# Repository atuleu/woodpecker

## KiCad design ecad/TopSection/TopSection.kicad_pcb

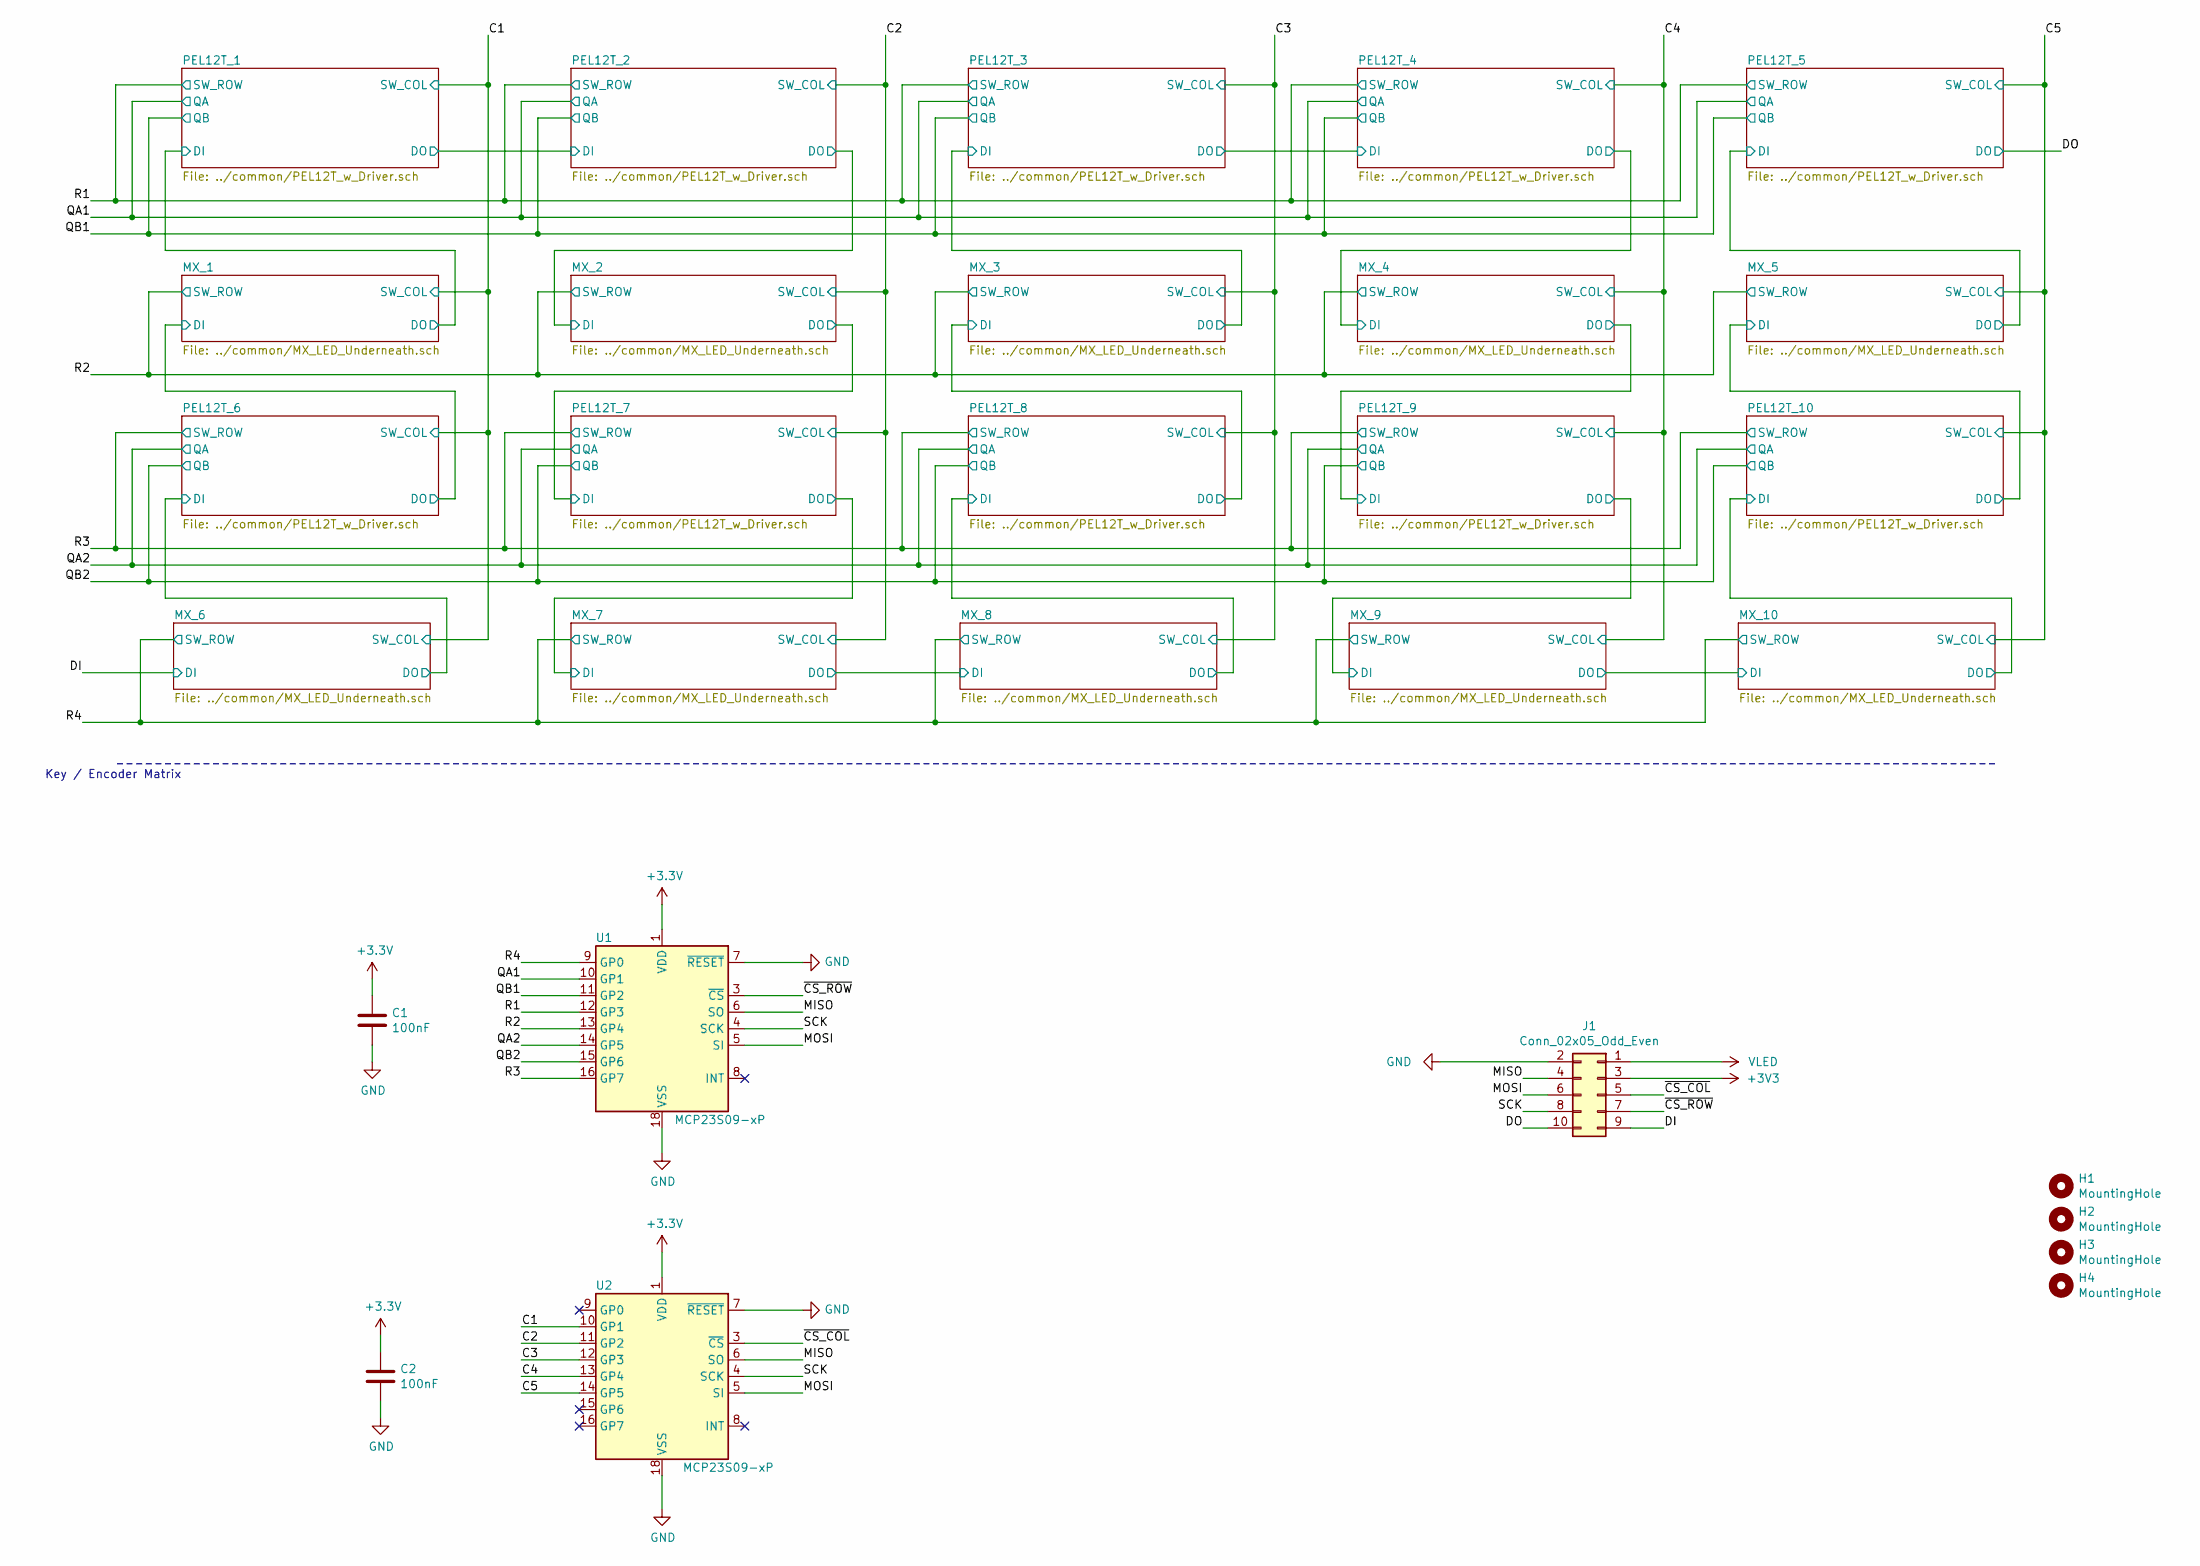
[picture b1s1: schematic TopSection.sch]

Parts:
C1, C2: 100nF; C_0603_1608Metric_Pad1.08x0.95mm_HandSolder
H1, H2, H3, H4: MountingHole; MountingHole_3.2mm_M3_DIN965
J1: Conn_02x05_Odd_Even; ConnectorMicromatch-10
U1, U2: MCP23S09-xP; DIP-18_W7.62mm

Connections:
/C1: U2.10 (GP1); also elsewhere on the board
/C2: U2.11 (GP2); also elsewhere on the board
/C3: U2.12 (GP3); also elsewhere on the board
/C4: U2.13 (GP4); also elsewhere on the board
/C5: U2.14 (GP5); also elsewhere on the board
/DI: J1.9; also elsewhere on the board
/DO: J1.10; also elsewhere on the board
/MISO: J1.4, U1.6 (SO), U2.6 (SO)
/MOSI: J1.6, U1.5 (SI), U2.5 (SI)
/QA1: U1.10 (GP1); also elsewhere on the board
/QA2: U1.14 (GP5); also elsewhere on the board
/QB1: U1.11 (GP2); also elsewhere on the board
/QB2: U1.15 (GP6); also elsewhere on the board
/R1: U1.12 (GP3); also elsewhere on the board
/R2: U1.13 (GP4); also elsewhere on the board
/R3: U1.16 (GP7); also elsewhere on the board
/R4: U1.9 (GP0); also elsewhere on the board
/SCK: J1.8, U1.4 (SCK), U2.4 (SCK)
/~CS_COL: J1.5, U2.3 (~CS)
/~CS_ROW: J1.7, U1.3 (~CS)
GND: C1.2, C2.2, J1.2, U1.7 (~RESET), U1.18 (VSS), U2.7 (~RESET), U2.18 (VSS); also elsewhere on the board
VLED: J1.1; also elsewhere on the board

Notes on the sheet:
Key / Encoder Matrix

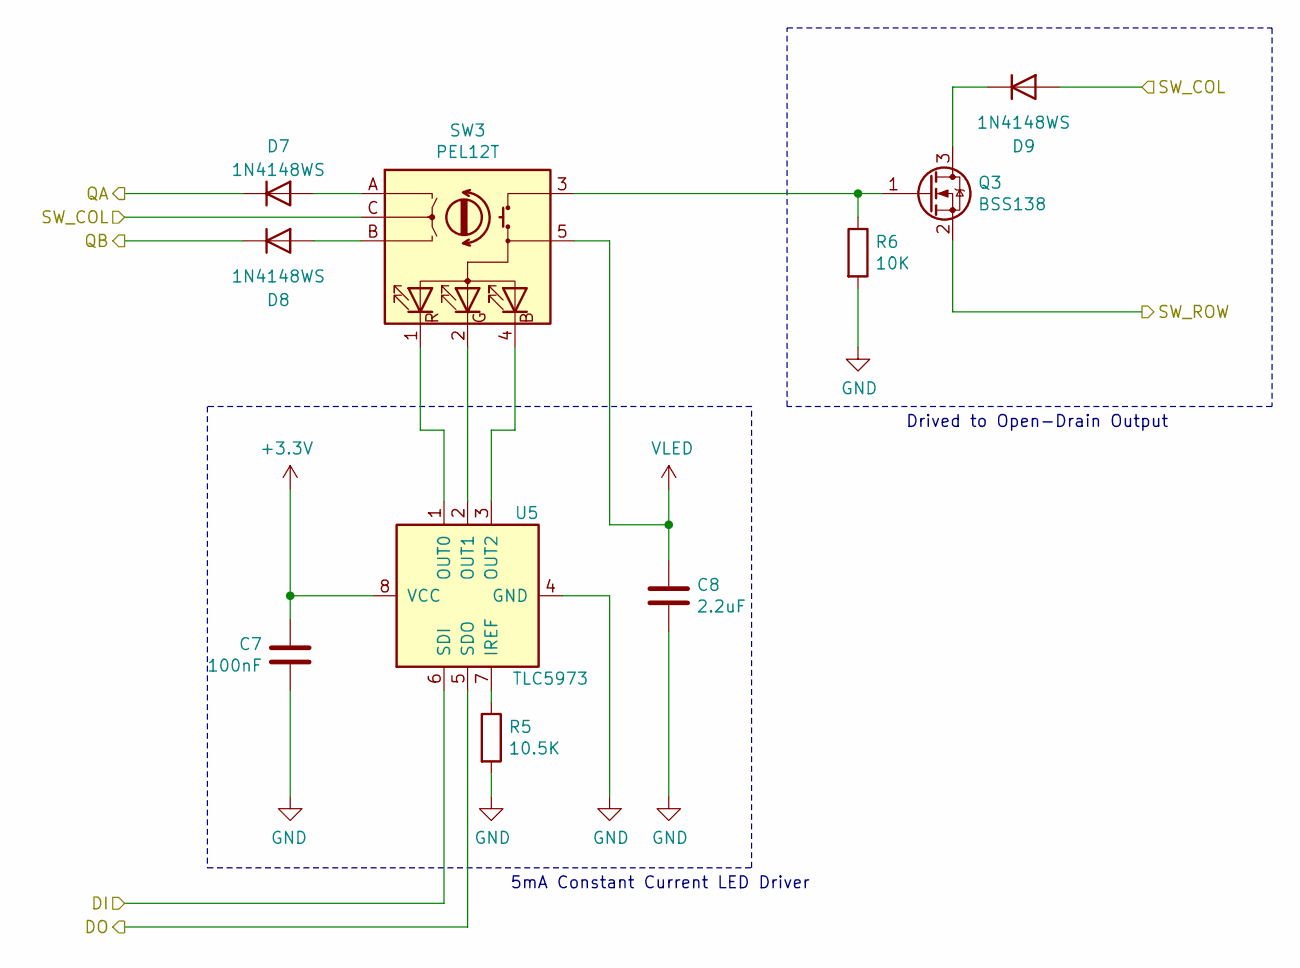
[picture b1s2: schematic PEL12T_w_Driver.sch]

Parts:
C3: 100nF; C_0603_1608Metric_Pad1.08x0.95mm_HandSolder
C4: 2.2uF; C_0805_2012Metric_Pad1.18x1.45mm_HandSolder
D1, D2, D3: 1N4148WS; D_SOD-323_HandSoldering
Q1: BSS138; SOT-23
R1: 10.5K; R_0603_1608Metric_Pad0.98x0.95mm_HandSolder
R2: 10K; R_0603_1608Metric_Pad0.98x0.95mm_HandSolder
SW1: PEL12T; PEL12T-4xxxS-S1024
U3: TLC5973; SOIC-8_3.9x4.9mm_P1.27mm

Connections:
/C1: D3.2 (A), SW1.C; also elsewhere on the board
/PEL12T_1/DI: U3.6 (SDI); also elsewhere on the board
/PEL12T_2/DI: U3.5 (SDO); also elsewhere on the board
/QA1: D1.1 (K); also elsewhere on the board
/QB1: D2.1 (K); also elsewhere on the board
/R1: Q1.2 (S); also elsewhere on the board
GND: C3.2, C4.2, R1.2, R2.2, U3.4 (GND); also elsewhere on the board
unnamed: D1.2 (A), SW1.A
unnamed: D2.2 (A), SW1.B
unnamed: D3.1 (K), Q1.3 (D)
unnamed: Q1.1 (G), R2.1, SW1.3
unnamed: R1.1, U3.7 (IREF)
unnamed: SW1.1 (RK), U3.1 (OUT0)
unnamed: SW1.2 (GK), U3.2 (OUT1)
unnamed: SW1.4 (BK), U3.3 (OUT2)
VLED: C4.1, SW1.5 (A); also elsewhere on the board

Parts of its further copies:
C5, C7, C9, C11, C23, C25, C27, C29, C31: 100nF; C_0603_1608Metric_Pad1.08x0.95mm_HandSolder
C6, C8, C10, C12, C24, C26, C28, C30, C32: 2.2uF; C_0805_2012Metric_Pad1.18x1.45mm_HandSolder
D4, D5, D6, D7, D8, D9, D10, D11, D12, D13, D14, D15, D21, D22, D23, D24, D25, D26, D27, D28, D29, D30, D31, D32, D33, D34, D35: 1N4148WS; D_SOD-323_HandSoldering
Q2, Q3, Q4, Q5, Q6, Q7, Q8, Q9, Q10: BSS138; SOT-23
R3, R7, R9, R16, R18, R20, R22, R24: 10.5K; R_0603_1608Metric_Pad0.98x0.95mm_HandSolder
R4, R6, R8, R10, R17, R19, R21, R23, R25: 10K; R_0603_1608Metric_Pad0.98x0.95mm_HandSolder
SW2, SW3, SW4, SW5, SW11, SW12, SW13, SW14, SW15: PEL12T; PEL12T-4xxxS-S1024
U4, U5, U6, U7, U10, U13, U14, U15, U16, U17: TLC5973; SOIC-8_3.9x4.9mm_P1.27mm

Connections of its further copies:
/C1: D23.2 (A), SW11.C; also elsewhere on the board
/C2: D6.2 (A), D26.2 (A), SW2.C, SW12.C; also elsewhere on the board
/C3: D9.2 (A), D29.2 (A), SW3.C, SW13.C; also elsewhere on the board
/C4: D12.2 (A), D32.2 (A), SW4.C, SW14.C; also elsewhere on the board
/C5: D15.2 (A), D35.2 (A), SW5.C, SW15.C; also elsewhere on the board
/DO: U7.5 (SDO); also elsewhere on the board
/MX_1/DI: U13.5 (SDO); also elsewhere on the board
/MX_2/DI: U4.5 (SDO); also elsewhere on the board
/MX_3/DI: U10.6 (SDI), U15.5 (SDO)
/MX_4/DI: U6.5 (SDO); also elsewhere on the board
/MX_5/DI: U17.5 (SDO); also elsewhere on the board
/MX_7/DI: U14.5 (SDO); also elsewhere on the board
/MX_9/DI: U16.5 (SDO); also elsewhere on the board
/PEL12T_2/DI: U4.6 (SDI); also elsewhere on the board
/PEL12T_3/DI: U5.6 (SDI), U10.5 (SDO)
/PEL12T_4/DI: U5.5 (SDO), U6.6 (SDI)
/PEL12T_5/DI: U7.6 (SDI); also elsewhere on the board
/PEL12T_6/DI: U13.6 (SDI); also elsewhere on the board
/PEL12T_7/DI: U14.6 (SDI); also elsewhere on the board
/PEL12T_8/DI: U15.6 (SDI); also elsewhere on the board
/PEL12T_9/DI: U16.6 (SDI); also elsewhere on the board
/PEL12T_10/DI: U17.6 (SDI); also elsewhere on the board
/QA1: D4.1 (K), D7.1 (K), D10.1 (K), D13.1 (K); also elsewhere on the board
/QA2: D21.1 (K), D24.1 (K), D27.1 (K), D30.1 (K), D33.1 (K); also elsewhere on the board
/QB1: D5.1 (K), D8.1 (K), D11.1 (K), D14.1 (K); also elsewhere on the board
/QB2: D22.1 (K), D25.1 (K), D28.1 (K), D31.1 (K), D34.1 (K); also elsewhere on the board
/R1: Q2.2 (S), Q3.2 (S), Q4.2 (S), Q5.2 (S); also elsewhere on the board
/R3: Q6.2 (S), Q7.2 (S), Q8.2 (S), Q9.2 (S), Q10.2 (S); also elsewhere on the board
GND: C5.2, C6.2, C7.2, C8.2, C9.2, C10.2, C11.2, C12.2, C23.2, C24.2, C25.2, C26.2, C27.2, C28.2, C29.2, C30.2, C31.2, C32.2, R3.2, R4.2, R6.2, R7.2, R8.2, R9.2, R10.2, R16.2, R17.2, R18.2, R19.2, R20.2, R21.2, R22.2, R23.2, R24.2, R25.2, U4.4 (GND), U5.4 (GND), U6.4 (GND), U7.4 (GND), U10.4 (GND), U13.4 (GND), U14.4 (GND), U15.4 (GND), U16.4 (GND), U17.4 (GND); also elsewhere on the board
unnamed: D4.2 (A), SW2.A
unnamed: D5.2 (A), SW2.B
unnamed: D6.1 (K), Q2.3 (D)
unnamed: D7.2 (A), SW3.A
unnamed: D8.2 (A), SW3.B
unnamed: D9.1 (K), Q3.3 (D)
unnamed: D10.2 (A), SW4.A
unnamed: D11.2 (A), SW4.B
unnamed: D12.1 (K), Q4.3 (D)
unnamed: D13.2 (A), SW5.A
unnamed: D14.2 (A), SW5.B
unnamed: D15.1 (K), Q5.3 (D)
unnamed: D21.2 (A), SW11.A
unnamed: D22.2 (A), SW11.B
unnamed: D23.1 (K), Q6.3 (D)
unnamed: D24.2 (A), SW12.A
unnamed: D25.2 (A), SW12.B
unnamed: D26.1 (K), Q7.3 (D)
unnamed: D27.2 (A), SW13.A
unnamed: D28.2 (A), SW13.B
unnamed: D29.1 (K), Q8.3 (D)
unnamed: D30.2 (A), SW14.A
unnamed: D31.2 (A), SW14.B
unnamed: D32.1 (K), Q9.3 (D)
unnamed: D33.2 (A), SW15.A
unnamed: D34.2 (A), SW15.B
unnamed: D35.1 (K), Q10.3 (D)
unnamed: Q2.1 (G), R4.1, SW2.3
unnamed: Q3.1 (G), R6.1, SW3.3
unnamed: Q4.1 (G), R8.1, SW4.3
unnamed: Q5.1 (G), R10.1, SW5.3
unnamed: Q6.1 (G), R17.1, SW11.3
unnamed: Q7.1 (G), R19.1, SW12.3
unnamed: Q8.1 (G), R21.1, SW13.3
unnamed: Q9.1 (G), R23.1, SW14.3
unnamed: Q10.1 (G), R25.1, SW15.3
unnamed: R3.1, U4.7 (IREF)
unnamed 92: U5.7 (IREF); also elsewhere on the board
unnamed: R7.1, U6.7 (IREF)
unnamed: R9.1, U7.7 (IREF)
unnamed 97: U10.7 (IREF); also elsewhere on the board
unnamed: R16.1, U13.7 (IREF)
unnamed: R18.1, U14.7 (IREF)
unnamed: R20.1, U15.7 (IREF)
unnamed: R22.1, U16.7 (IREF)
unnamed: R24.1, U17.7 (IREF)
unnamed: SW2.1 (RK), U4.1 (OUT0)
unnamed: SW2.2 (GK), U4.2 (OUT1)
unnamed: SW2.4 (BK), U4.3 (OUT2)
unnamed: SW3.1 (RK), U5.1 (OUT0)
unnamed: SW3.2 (GK), U5.2 (OUT1)
unnamed: SW3.4 (BK), U5.3 (OUT2)
unnamed: SW4.1 (RK), U6.1 (OUT0)
unnamed: SW4.2 (GK), U6.2 (OUT1)
unnamed: SW4.4 (BK), U6.3 (OUT2)
unnamed: SW5.1 (RK), U7.1 (OUT0)
unnamed: SW5.2 (GK), U7.2 (OUT1)
unnamed: SW5.4 (BK), U7.3 (OUT2)
unnamed 131: U10.3 (OUT2); also elsewhere on the board
unnamed 132: U10.2 (OUT1); also elsewhere on the board
unnamed 133: U10.1 (OUT0); also elsewhere on the board
unnamed: SW11.1 (RK), U13.1 (OUT0)
unnamed: SW11.2 (GK), U13.2 (OUT1)
unnamed: SW11.4 (BK), U13.3 (OUT2)
unnamed: SW12.1 (RK), U14.1 (OUT0)
unnamed: SW12.2 (GK), U14.2 (OUT1)
unnamed: SW12.4 (BK), U14.3 (OUT2)
unnamed: SW13.1 (RK), U15.1 (OUT0)
unnamed: SW13.2 (GK), U15.2 (OUT1)
unnamed: SW13.4 (BK), U15.3 (OUT2)
unnamed: SW14.1 (RK), U16.1 (OUT0)
unnamed: SW14.2 (GK), U16.2 (OUT1)
unnamed: SW14.4 (BK), U16.3 (OUT2)
unnamed: SW15.1 (RK), U17.1 (OUT0)
unnamed: SW15.2 (GK), U17.2 (OUT1)
unnamed: SW15.4 (BK), U17.3 (OUT2)
VLED: C6.1, C8.1, C10.1, C12.1, C24.1, C26.1, C28.1, C30.1, C32.1, SW2.5 (A), SW3.5 (A), SW4.5 (A), SW5.5 (A), SW11.5 (A), SW12.5 (A), SW13.5 (A), SW14.5 (A), SW15.5 (A); also elsewhere on the board

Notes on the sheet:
5mA Constant Current LED Driver
Drived to Open-Drain Output

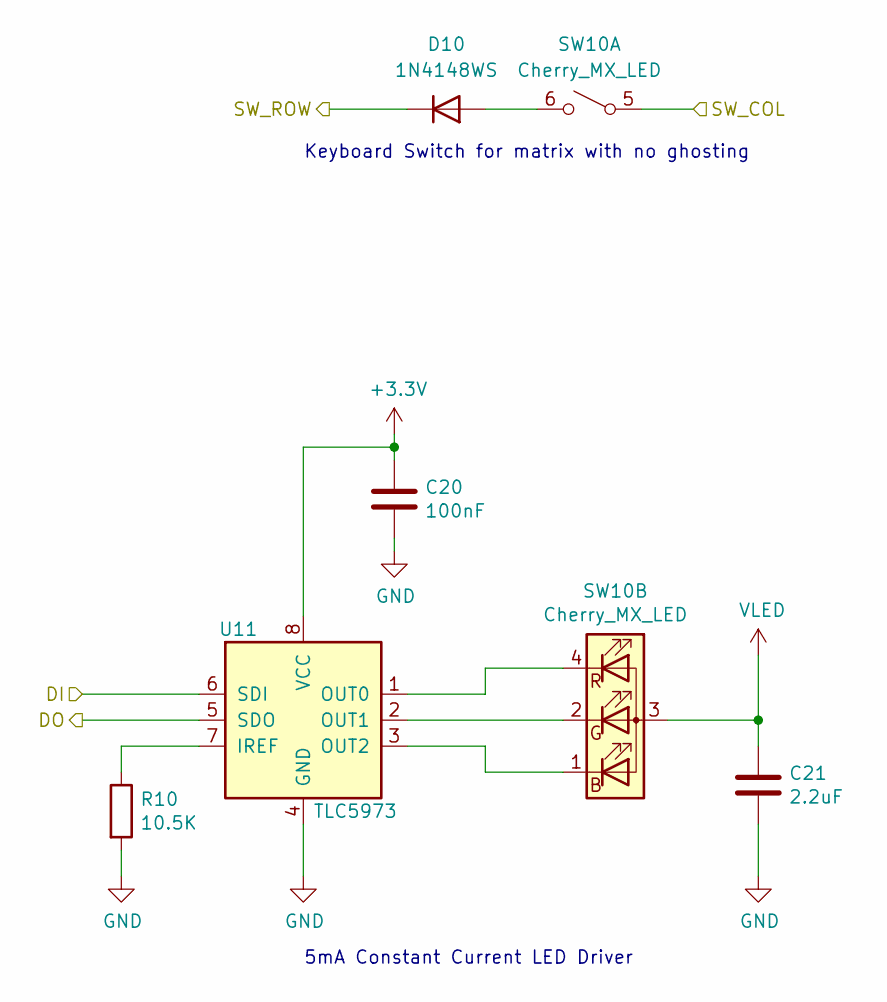
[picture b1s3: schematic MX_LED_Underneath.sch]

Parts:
C13: 100nF; C_0603_1608Metric_Pad1.08x0.95mm_HandSolder
C14: 2.2uF; C_0805_2012Metric_Pad1.18x1.45mm_HandSolder
D16: 1N4148WS; D_SOD-323_HandSoldering
R11: 10.5K; R_0603_1608Metric_Pad0.98x0.95mm_HandSolder
SW6: Cherry_MX_LED; SW_Cherry_MX_1.00u_PCB_SMD_LED
U8: TLC5973; SOIC-8_3.9x4.9mm_P1.27mm

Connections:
/C1: SW6.5 (SW_A); also elsewhere on the board
/MX_1/DI: U8.6 (SDI); also elsewhere on the board
/PEL12T_1/DI: U8.5 (SDO); also elsewhere on the board
/R2: D16.1 (K); also elsewhere on the board
GND: C13.2, C14.2, R11.2, U8.4 (GND); also elsewhere on the board
unnamed: D16.2 (A), SW6.6 (SW_B)
unnamed: R11.1, U8.7 (IREF)
unnamed: SW6.1 (BK), U8.3 (OUT2)
unnamed: SW6.2 (GK), U8.2 (OUT1)
unnamed: SW6.4 (RK), U8.1 (OUT0)
VLED: C14.1, SW6.3 (A); also elsewhere on the board

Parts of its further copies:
C5, C9, C15, C17, C19, C21, C33, C35, C37, C39, C41: 100nF; C_0603_1608Metric_Pad1.08x0.95mm_HandSolder
C22, C34, C36, C38, C40, C42: 2.2uF; C_0805_2012Metric_Pad1.18x1.45mm_HandSolder
D4, D5, D6, D7, D8, D9, D10, D17, D18, D19, D20, D36, D37, D38, D39, D40: 1N4148WS; D_SOD-323_HandSoldering
R3, R5, R7, R9, R12, R13, R14, R15, R26, R27, R28, R29, R30: 10.5K; R_0603_1608Metric_Pad0.98x0.95mm_HandSolder
SW7, SW8, SW9, SW10, SW16, SW17, SW18, SW19, SW20: Cherry_MX_LED; SW_Cherry_MX_1.00u_PCB_SMD_LED
U4, U5, U6, U7, U9, U10, U11, U12, U18, U19, U20, U21, U22: TLC5973; SOIC-8_3.9x4.9mm_P1.27mm

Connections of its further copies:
/C1: SW16.5 (SW_A); also elsewhere on the board
/C2: D6.2 (A), SW7.5 (SW_A), SW17.5 (SW_A); also elsewhere on the board
/C3: D9.2 (A), SW8.5 (SW_A), SW18.5 (SW_A); also elsewhere on the board
/C4: SW9.5 (SW_A), SW19.5 (SW_A); also elsewhere on the board
/C5: SW10.5 (SW_A), SW20.5 (SW_A); also elsewhere on the board
/DI: U18.6 (SDI); also elsewhere on the board
/DO: U7.5 (SDO); also elsewhere on the board
/MX_2/DI: U4.5 (SDO), U9.6 (SDI)
/MX_3/DI: U10.6 (SDI); also elsewhere on the board
/MX_4/DI: U6.5 (SDO), U11.6 (SDI)
/MX_5/DI: U12.6 (SDI); also elsewhere on the board
/MX_7/DI: U19.6 (SDI); also elsewhere on the board
/MX_8/DI: U19.5 (SDO), U20.6 (SDI)
/MX_9/DI: U21.6 (SDI); also elsewhere on the board
/MX_10/DI: U21.5 (SDO), U22.6 (SDI)
/PEL12T_2/DI: U4.6 (SDI); also elsewhere on the board
/PEL12T_3/DI: U5.6 (SDI), U10.5 (SDO)
/PEL12T_4/DI: U5.5 (SDO), U6.6 (SDI)
/PEL12T_5/DI: U7.6 (SDI), U12.5 (SDO)
/PEL12T_6/DI: U18.5 (SDO); also elsewhere on the board
/PEL12T_7/DI: U9.5 (SDO); also elsewhere on the board
/PEL12T_8/DI: U20.5 (SDO); also elsewhere on the board
/PEL12T_9/DI: U11.5 (SDO); also elsewhere on the board
/PEL12T_10/DI: U22.5 (SDO); also elsewhere on the board
/QA1: D4.1 (K), D7.1 (K), D10.1 (K); also elsewhere on the board
/QB1: D5.1 (K), D8.1 (K); also elsewhere on the board
/R2: D17.1 (K), D18.1 (K), D19.1 (K), D20.1 (K); also elsewhere on the board
/R4: D36.1 (K), D37.1 (K), D38.1 (K), D39.1 (K), D40.1 (K); also elsewhere on the board
GND: C5.2, C9.2, C15.2, C17.2, C19.2, C21.2, C22.2, C33.2, C34.2, C35.2, C36.2, C37.2, C38.2, C39.2, C40.2, C41.2, C42.2, R3.2, R5.2, R7.2, R9.2, R12.2, R13.2, R14.2, R15.2, R26.2, R27.2, R28.2, R29.2, R30.2, U4.4 (GND), U5.4 (GND), U6.4 (GND), U7.4 (GND), U9.4 (GND), U10.4 (GND), U11.4 (GND), U12.4 (GND), U18.4 (GND), U19.4 (GND), U20.4 (GND), U21.4 (GND), U22.4 (GND); also elsewhere on the board
unnamed 43: D4.2 (A); also elsewhere on the board
unnamed 44: D5.2 (A); also elsewhere on the board
unnamed 45: D6.1 (K); also elsewhere on the board
unnamed 46: D7.2 (A); also elsewhere on the board
unnamed 47: D8.2 (A); also elsewhere on the board
unnamed 48: D9.1 (K); also elsewhere on the board
unnamed 49: D10.2 (A); also elsewhere on the board
unnamed: D17.2 (A), SW7.6 (SW_B)
unnamed: D18.2 (A), SW8.6 (SW_B)
unnamed: D19.2 (A), SW9.6 (SW_B)
unnamed: D20.2 (A), SW10.6 (SW_B)
unnamed: D36.2 (A), SW16.6 (SW_B)
unnamed: D37.2 (A), SW17.6 (SW_B)
unnamed: D38.2 (A), SW18.6 (SW_B)
unnamed: D39.2 (A), SW19.6 (SW_B)
unnamed: D40.2 (A), SW20.6 (SW_B)
unnamed: R3.1, U4.7 (IREF)
unnamed: R5.1, U5.7 (IREF)
unnamed: R7.1, U6.7 (IREF)
unnamed: R9.1, U7.7 (IREF)
unnamed: R12.1, U9.7 (IREF)
unnamed: R13.1, U10.7 (IREF)
unnamed: R14.1, U11.7 (IREF)
unnamed: R15.1, U12.7 (IREF)
unnamed: R26.1, U18.7 (IREF)
unnamed: R27.1, U19.7 (IREF)
unnamed: R28.1, U20.7 (IREF)
unnamed: R29.1, U21.7 (IREF)
unnamed: R30.1, U22.7 (IREF)
unnamed 113: U4.1 (OUT0); also elsewhere on the board
unnamed 114: U4.2 (OUT1); also elsewhere on the board
unnamed 115: U4.3 (OUT2); also elsewhere on the board
unnamed 116: U5.1 (OUT0); also elsewhere on the board
unnamed 117: U5.2 (OUT1); also elsewhere on the board
unnamed 118: U5.3 (OUT2); also elsewhere on the board
unnamed 119: U6.1 (OUT0); also elsewhere on the board
unnamed 120: U6.2 (OUT1); also elsewhere on the board
unnamed 121: U6.3 (OUT2); also elsewhere on the board
unnamed 122: U7.1 (OUT0); also elsewhere on the board
unnamed 123: U7.2 (OUT1); also elsewhere on the board
unnamed 124: U7.3 (OUT2); also elsewhere on the board
unnamed: SW7.1 (BK), U9.3 (OUT2)
unnamed: SW7.2 (GK), U9.2 (OUT1)
unnamed: SW7.4 (RK), U9.1 (OUT0)
unnamed: SW8.1 (BK), U10.3 (OUT2)
unnamed: SW8.2 (GK), U10.2 (OUT1)
unnamed: SW8.4 (RK), U10.1 (OUT0)
unnamed: SW9.1 (BK), U11.3 (OUT2)
unnamed: SW9.2 (GK), U11.2 (OUT1)
unnamed: SW9.4 (RK), U11.1 (OUT0)
unnamed: SW10.1 (BK), U12.3 (OUT2)
unnamed: SW10.2 (GK), U12.2 (OUT1)
unnamed: SW10.4 (RK), U12.1 (OUT0)
unnamed: SW16.1 (BK), U18.3 (OUT2)
unnamed: SW16.2 (GK), U18.2 (OUT1)
unnamed: SW16.4 (RK), U18.1 (OUT0)
unnamed: SW17.1 (BK), U19.3 (OUT2)
unnamed: SW17.2 (GK), U19.2 (OUT1)
unnamed: SW17.4 (RK), U19.1 (OUT0)
unnamed: SW18.1 (BK), U20.3 (OUT2)
unnamed: SW18.2 (GK), U20.2 (OUT1)
unnamed: SW18.4 (RK), U20.1 (OUT0)
unnamed: SW19.1 (BK), U21.3 (OUT2)
unnamed: SW19.2 (GK), U21.2 (OUT1)
unnamed: SW19.4 (RK), U21.1 (OUT0)
unnamed: SW20.1 (BK), U22.3 (OUT2)
unnamed: SW20.2 (GK), U22.2 (OUT1)
unnamed: SW20.4 (RK), U22.1 (OUT0)
VLED: C22.1, C34.1, C36.1, C38.1, C40.1, C42.1, SW7.3 (A), SW8.3 (A), SW9.3 (A), SW10.3 (A), SW16.3 (A), SW17.3 (A), SW18.3 (A), SW19.3 (A), SW20.3 (A); also elsewhere on the board

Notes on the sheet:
5mA Constant Current LED Driver
Keyboard Switch for matrix with no ghosting

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
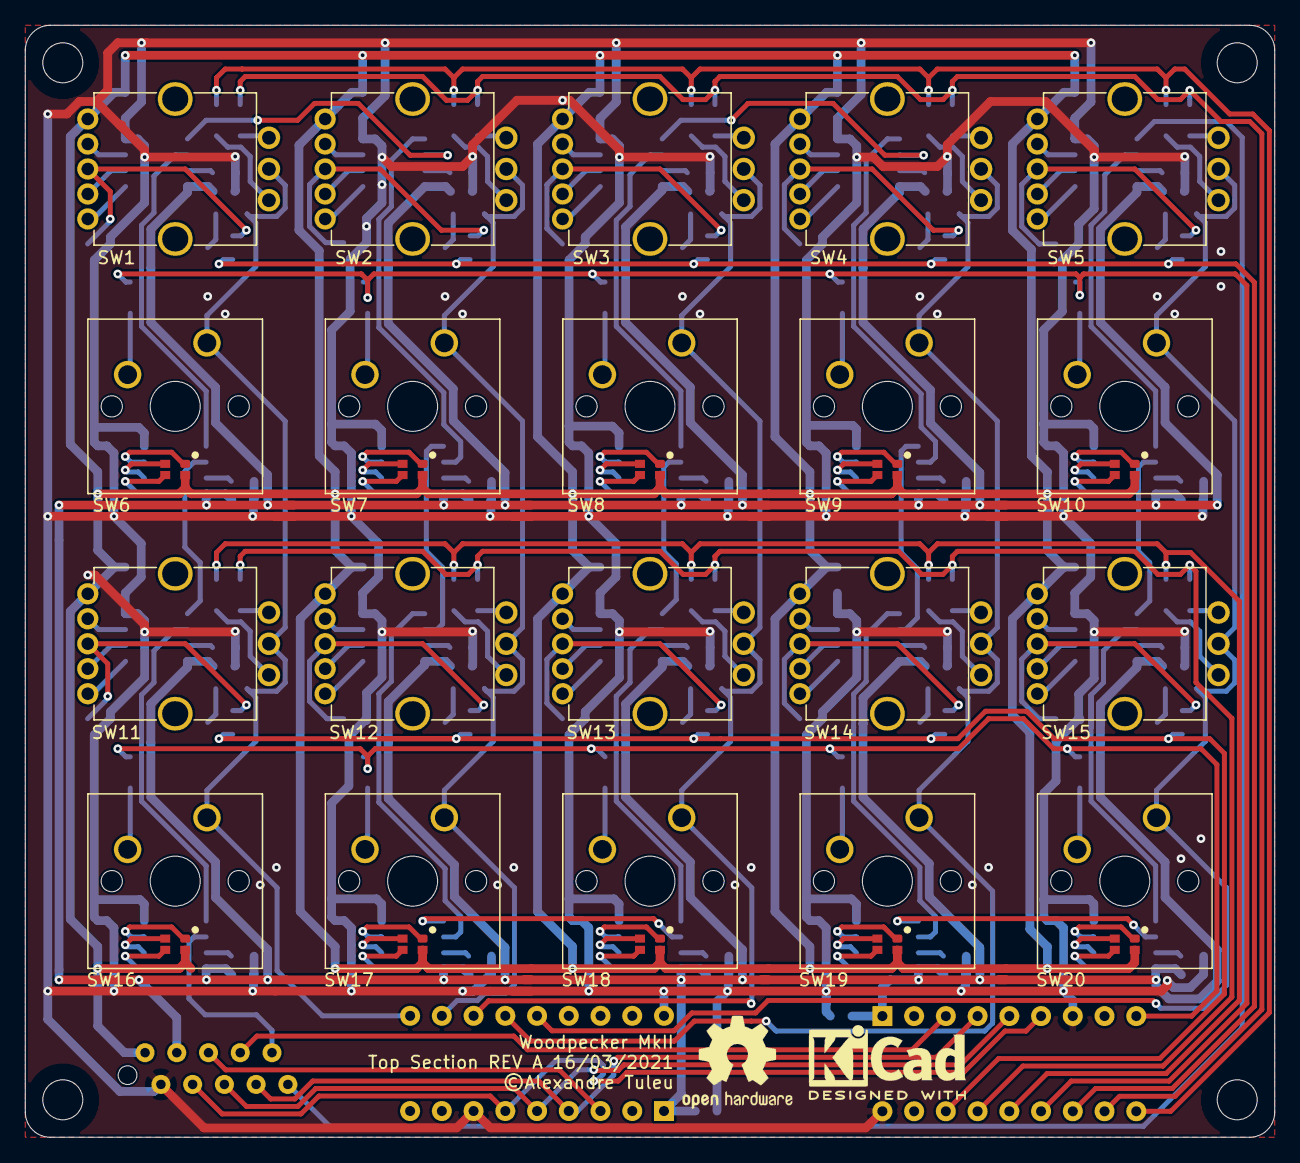
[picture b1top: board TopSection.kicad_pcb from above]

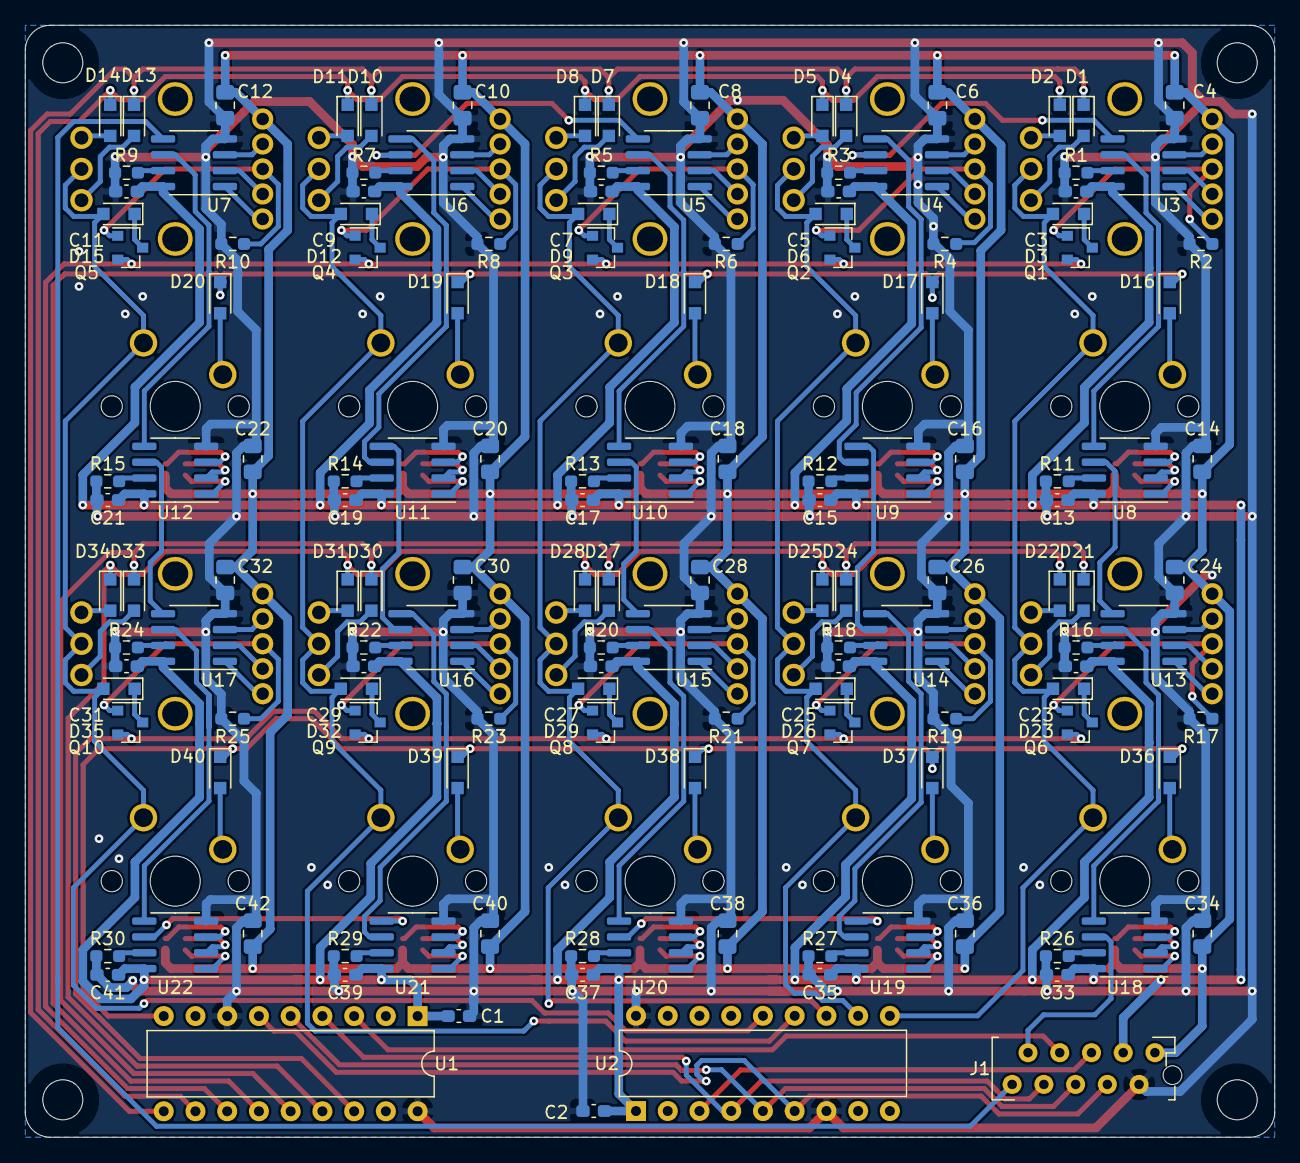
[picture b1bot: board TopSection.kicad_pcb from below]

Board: 2 copper layers, 100.0 x 89.0 mm, 169 parts (145 on the bottom side), 172 nets.

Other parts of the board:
C16, C18, C20: 2.2uF; C_0805_2012Metric_Pad1.18x1.45mm_HandSolder

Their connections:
GND: C16.2, C18.2, C20.2; also elsewhere on the board
VLED: C16.1, C18.1, C20.1; also elsewhere on the board

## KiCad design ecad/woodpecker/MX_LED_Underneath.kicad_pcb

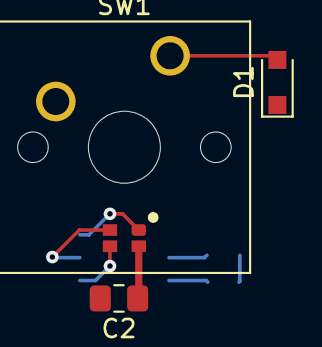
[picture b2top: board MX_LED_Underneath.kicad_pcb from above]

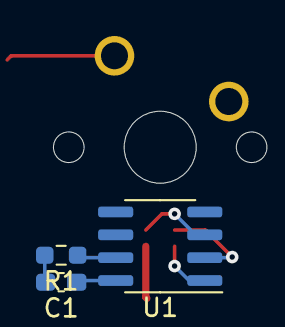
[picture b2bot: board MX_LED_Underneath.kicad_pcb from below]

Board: 2 copper layers, 6 parts (3 on the bottom side), 8 nets.

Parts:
C1: 100nF; C_0603_1608Metric_Pad1.08x0.95mm_HandSolder
C2: 2.2uF; C_0805_2012Metric_Pad1.18x1.45mm_HandSolder
D1: 1N4148WS; D_SOD-323_HandSoldering
R1: 10.5K; R_0603_1608Metric_Pad0.98x0.95mm_HandSolder
SW1: Cherry_MX_LED; SW_Cherry_MX_1.00u_PCB_SMD_LED
U1: TLC5973; SOIC-8_3.9x4.9mm_P1.27mm

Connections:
+3V3: C1.1, U1.8
GND: C1.2, C2.2, R1.2, U1.4
unnamed: D1.2, SW1.5
unnamed: R1.1, U1.7
unnamed: SW1.1, U1.3
unnamed: SW1.2, U1.2
unnamed: SW1.4, U1.1
VLED: C2.1, SW1.3

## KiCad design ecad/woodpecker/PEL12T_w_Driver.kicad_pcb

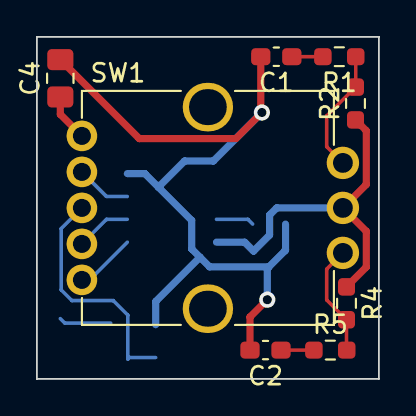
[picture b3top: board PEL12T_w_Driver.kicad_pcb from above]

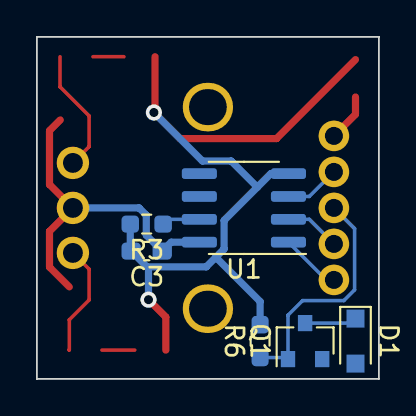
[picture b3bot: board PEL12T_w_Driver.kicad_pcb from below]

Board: 2 copper layers, 19.0 x 19.0 mm, 14 parts (6 on the bottom side), 13 nets.

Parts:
C1, C2: 10nF; C_0603_1608Metric_Pad1.08x0.95mm_HandSolder
C3: 100nF; C_0603_1608Metric_Pad1.08x0.95mm_HandSolder
C4: 2.2uF; C_0805_2012Metric_Pad1.18x1.45mm_HandSolder
D1: 1N4148WS; D_SOD-323_HandSoldering
Q1: BSS138; SOT-23
R1, R2, R4, R5: 10K; R_0603_1608Metric_Pad0.98x0.95mm_HandSolder
R3, R6: 10.5K; R_0603_1608Metric_Pad0.98x0.95mm_HandSolder
SW1: PEL12T; PEL12T-4xxxS-S1024
U1: TLC5973; SOIC-8_3.9x4.9mm_P1.27mm

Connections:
+3V3: C3.1, R2.1, R4.1, SW1.C, U1.8
/QA: C2.1, R5.1
/QB: C1.1, R1.2
GND: C1.2, C2.2, C3.2, C4.2, R3.2, R6.2, U1.4
unnamed: D1.1, Q1.3
unnamed: Q1.1, R6.1, SW1.3
unnamed: R1.1, R2.2, SW1.B
unnamed: R3.1, U1.7
unnamed: R4.2, R5.2, SW1.A
unnamed: SW1.1, U1.1
unnamed: SW1.2, U1.2
unnamed: SW1.4, U1.3
VLED: C4.1, SW1.5

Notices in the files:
ecad/TopSection/TopSection.kicad_pcb:
©Alexandre Tuleu
ecad/woodpecker/woodpecker.kicad_pcb:
©Alexandre Tuleu 2021
